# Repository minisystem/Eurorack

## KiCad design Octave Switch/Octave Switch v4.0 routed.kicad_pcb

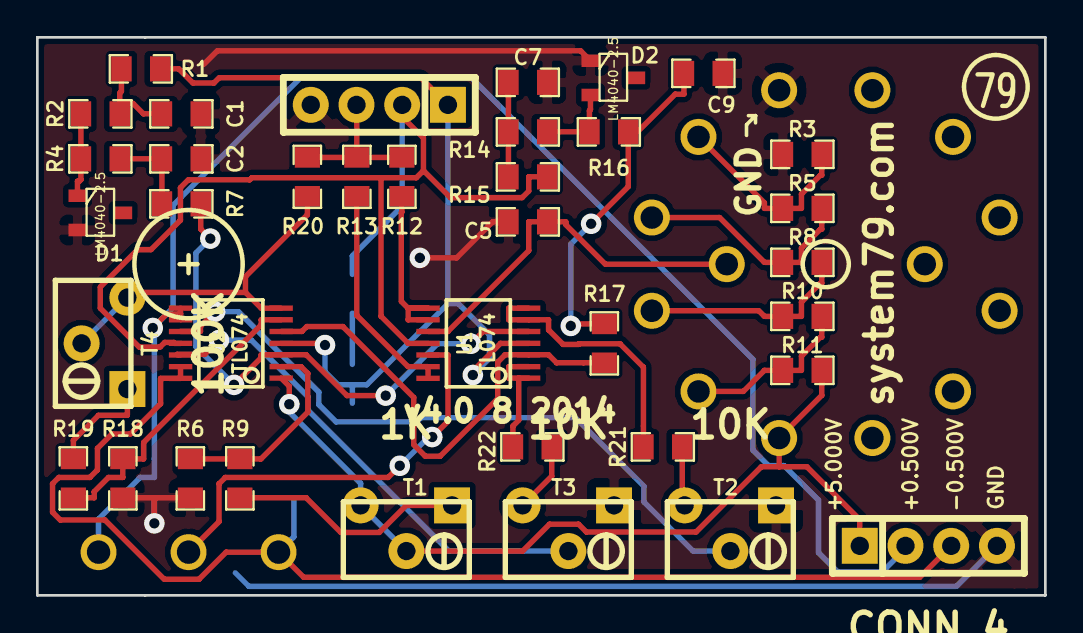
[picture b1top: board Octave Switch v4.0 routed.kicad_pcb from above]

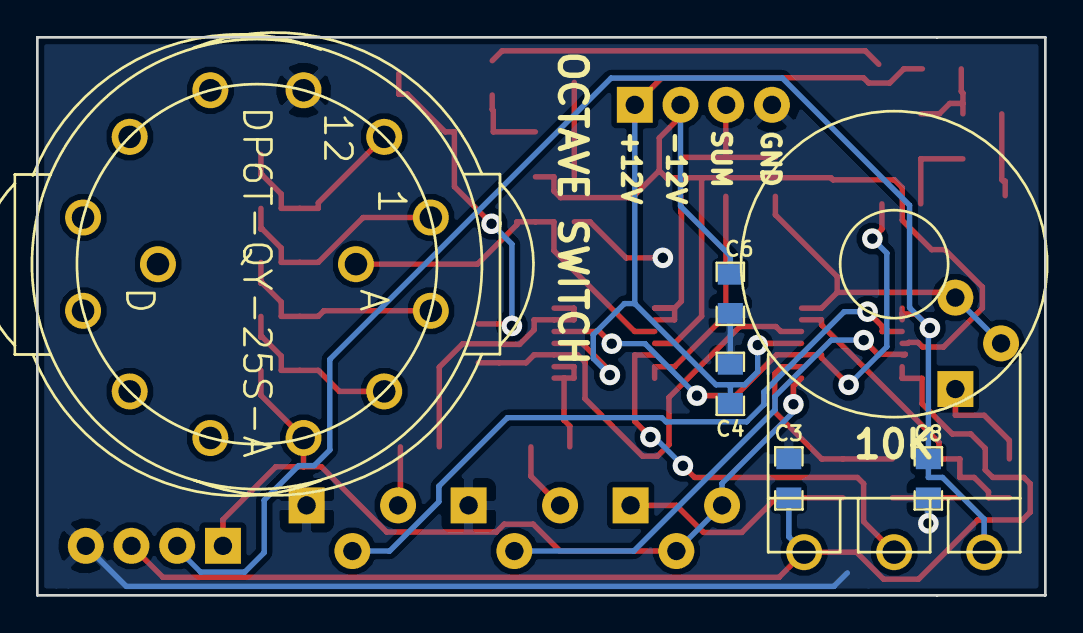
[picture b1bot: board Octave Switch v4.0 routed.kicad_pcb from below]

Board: 2 copper layers, 56.0 x 31.0 mm, 43 parts (6 on the bottom side), 34 nets.

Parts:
C1, C2, C4, C6, C7, C9: 0.1u; SM0805-HAND
C3, C5, C8: 0.001u; SM0805-HAND
D1, D2: LM4040-2.5; SOT23
P1, P2: CONN_4; CONN_0100_X_4
POT1: 10K; RV16A-41
R1, R2, R14, R15: 4.7K; SM0805-HAND
R3, R5, R6, R8, R10, R11: 10K; SM0805-HAND
R4, R7, R16, R17: 33K; SM0805-HAND
R9: 9.53K; SM0805-HAND
R12, R13, R18, R20: 100K; SM0805-HAND
R19: 49.9K; SM0805-HAND
R21, R22: 15K; SM0805-HAND
SW1: DP6T-QY-25S-A; QY-25S-2P6C-JRL
TRIM1: 1K; BI_64W_TRIM
TRIM2, TRIM3: 10K; BI_64W_TRIM
TRIM4: 100K; BI_64W_TRIM
U1, U2: TL074; TSSOP14

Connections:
+0.500V: C8.2, P1.2, POT1.3, U2.8, U2.9
+2.5V: R7.2, U1.5, U2.3
+5.00V: P1.1, R11.2, SW1.4, TRIM1.2, TRIM1.3, U2.1
+12V: C6.1, P2.1, R1.2, U1.4, U2.4
-0.500V: C3.2, P1.3, POT1.1, U2.13, U2.14
-2.5V: R17.2, U1.3, U2.5
-12V: C4.2, P2.2, R15.1, U1.11, U2.11
GND: C1.2, C2.2, C3.1, C4.1, C5.2, C6.2, C7.2, C8.1, C9.2, D1.2, D2.1, P1.4, P2.4, R3.1, R6.1, R18.1, SW1.11, TRIM2.1, TRIM3.1
unnamed: R13.1, U1.13, U1.14
unnamed: C5.1, SW1.A, U1.10
unnamed: D1.1, R2.1, R4.1
unnamed: C1.1, R1.1, R2.2
unnamed: C7.1, R14.1, R15.2
unnamed: D2.2, R14.2, R16.1
unnamed: C9.1, R16.2, R17.1
unnamed: POT1.2, U1.12
unnamed: R5.2, R8.1, SW1.1
unnamed: R8.2, R10.1, SW1.2
unnamed: R10.2, R11.1, SW1.3
unnamed: R12.1, U1.8, U1.9
unnamed: R3.2, R5.1, SW1.12
unnamed: R22.2, TRIM3.3
unnamed: R22.1, U1.1, U1.2
unnamed: R21.2, TRIM2.3
unnamed: R21.1, U1.6, U1.7
unnamed: TRIM3.2, U2.12
unnamed: TRIM2.2, U2.10
unnamed: R20.1, TRIM4.2, TRIM4.3, U2.7
unnamed: R19.2, TRIM4.1
unnamed: R9.2, TRIM1.1
unnamed: R6.2, R9.1, U2.2
unnamed: R18.2, R19.1, U2.6
unnamed: C2.1, R4.2, R7.1
SUM OUT: P2.3, R12.2, R13.2, R20.2

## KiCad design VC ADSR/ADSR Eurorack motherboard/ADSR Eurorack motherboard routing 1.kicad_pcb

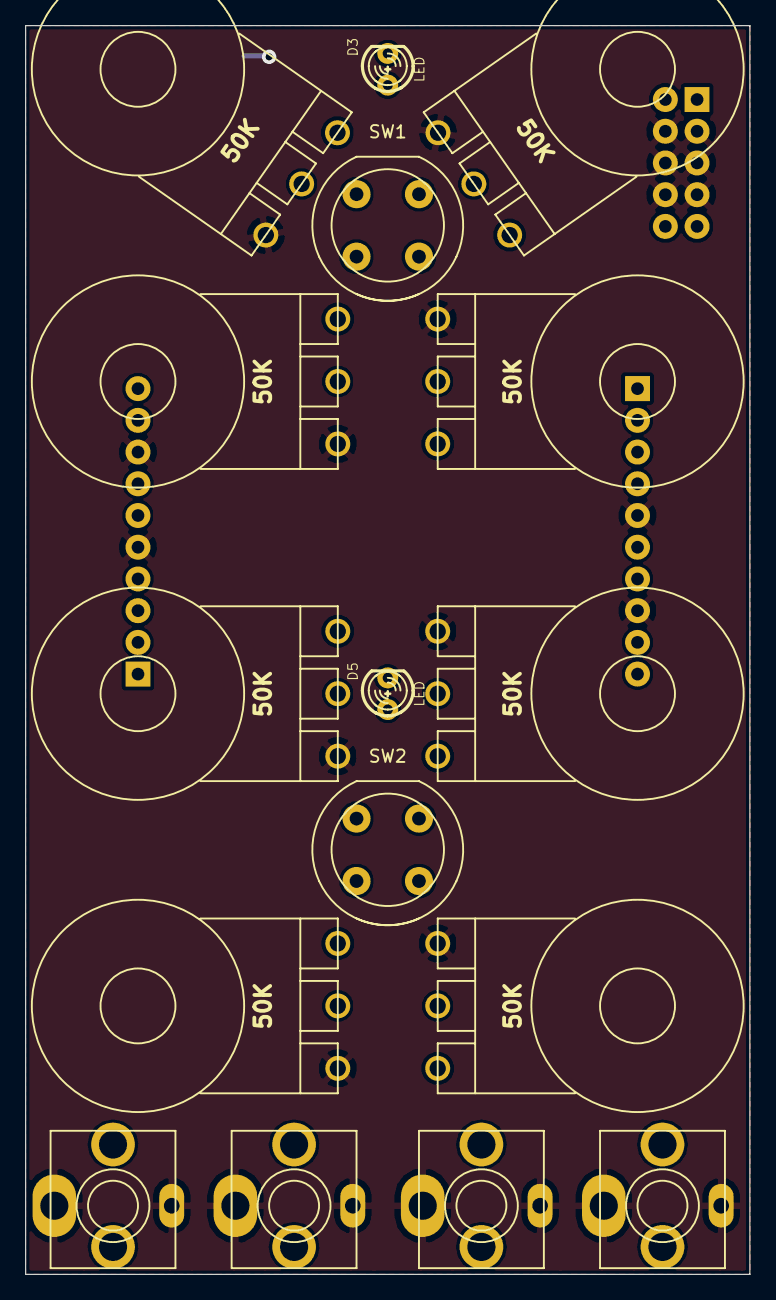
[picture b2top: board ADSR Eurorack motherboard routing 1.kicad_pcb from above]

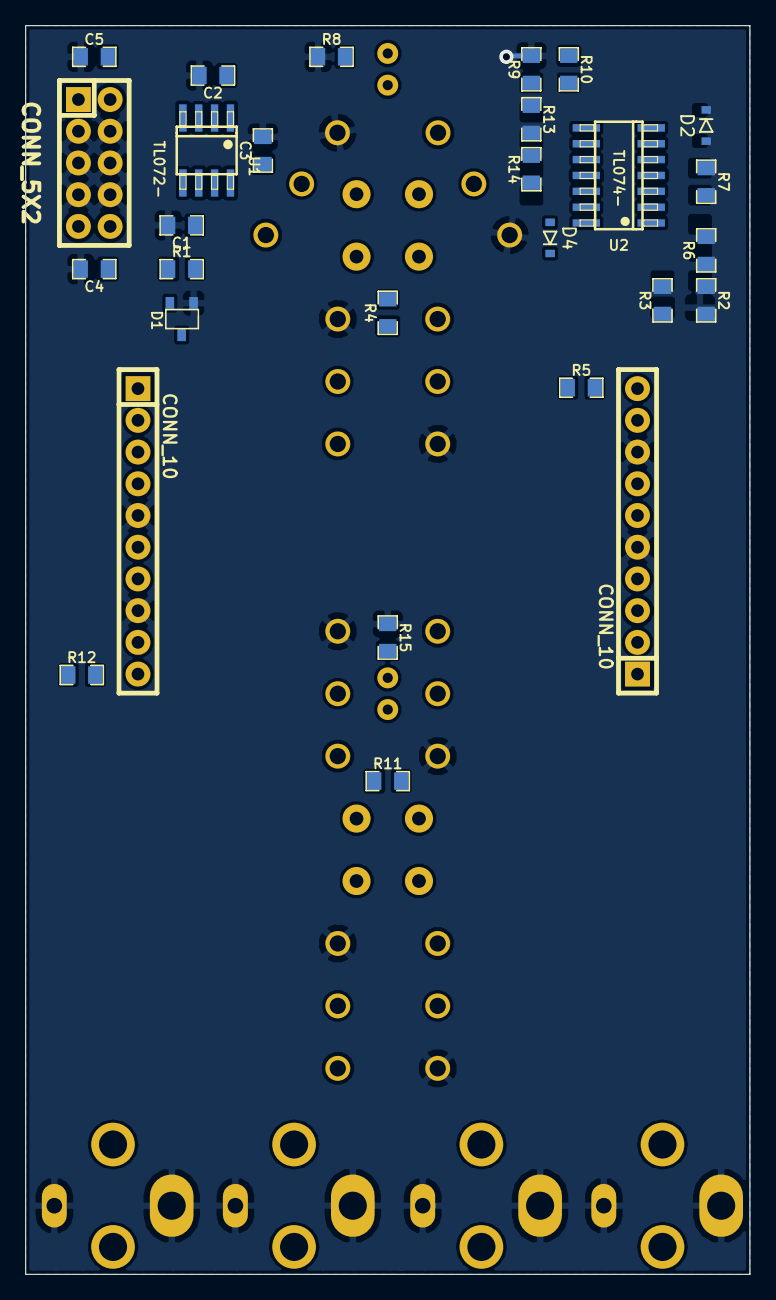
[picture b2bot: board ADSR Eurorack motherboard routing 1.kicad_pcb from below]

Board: 2 copper layers, 58.0 x 100.0 mm, 44 parts (28 on the bottom side), 34 nets.

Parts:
C1, C2, C3: 100n; SM0805-HAND
C4, C5: 1μ; SM0805-HAND
D1: LM4040-5.0; SOT23-JRL
D2, D4: 1N4148; SOD323-JRL
D3, D5: LED; LED-3MM
EG1, EG2: CONN_10; CONN_0100_X_10
J1, J3: OUT1; PJ-301B-JACK
J2, J4: GATE1; PJ-301B-JACK
P1, P2, P3, P4, P5, P6, P7, P8: 50K; RV16A-41
PWR1: CONN_5X2; CONN_0100_2X5_10
R1, R4, R5, R11, R12: 10K; SM0805-HAND
R2, R9: 120K; SM0805-HAND
R3, R10: 330K; SM0805-HAND
R6, R13: 100K; SM0805-HAND
R7, R14: 82K; SM0805-HAND
R8, R15: 270; SM0805-HAND
SW1, SW2: SW_PUSH; KS-01Q-02-JRL
U1: TL072-; SOIC-8-JRL
U2: TL074-; SO14-JRL

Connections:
+5.0V A: C2.1, P1.3, P2.3, P3.3, P4.3, R4.1, U1.1, U1.2
+5.0V B: C3.1, P5.3, P6.3, P7.3, P8.3, R11.1, U1.6, U1.7
+12V: C4.1, EG1.1, EG2.1, PWR1.9, PWR1.10, R1.1, U1.8, U2.4
-12V: C5.2, EG1.3, EG2.3, PWR1.1, PWR1.2, R3.1, R10.1, U1.4, U2.11
ATT1: EG1.9, P1.2
ATT2: EG2.9, P5.2
DEC1: EG1.2, P2.2
DEC2: EG2.2, P6.2
GATE1: EG1.10, R5.2, SW1.2, SW1.4
GATE2: EG2.10, R12.2, SW2.2, SW2.4
GND: C1.2, C2.2, C3.2, C4.2, C5.1, D1.2, EG1.5, EG1.8, EG2.5, EG2.8, J1.1, J2.1, J3.1, J4.1, P1.1, P2.1, P3.1, P4.1, P5.1, P6.1, P7.1, P8.1, PWR1.3, PWR1.4, PWR1.5, PWR1.6, PWR1.7, PWR1.8, R2.2, R8.1, R9.2, R15.1
unnamed: R11.2, SW2.1, SW2.3
unnamed: R2.1, R3.2, R6.1
unnamed: R6.2, R7.1, U2.2
unnamed: D5.2, R15.2
unnamed: R13.2, R14.1, U2.9
unnamed: D4.2, D5.1, U2.14
unnamed: D4.1, U2.13
unnamed: R4.2, SW1.1, SW1.3
unnamed: J4.3, R12.1
unnamed: R9.1, R10.2, R13.1
unnamed: R14.2, U2.8, U2.12
unnamed: J2.3, R5.1
unnamed: D2.1, U2.6
unnamed: R7.2, U2.1, U2.5
unnamed: C1.1, D1.1, R1.2, U1.3, U1.5
unnamed: D3.2, R8.2
unnamed: D2.2, D3.1, U2.7
OUT1: EG1.4, J1.3, U2.3
OUT2: EG2.4, J3.3, U2.10
REL1: EG1.7, P4.2
REL2: EG2.7, P8.2
SUS1: EG1.6, P3.2
SUS2: EG2.6, P7.2

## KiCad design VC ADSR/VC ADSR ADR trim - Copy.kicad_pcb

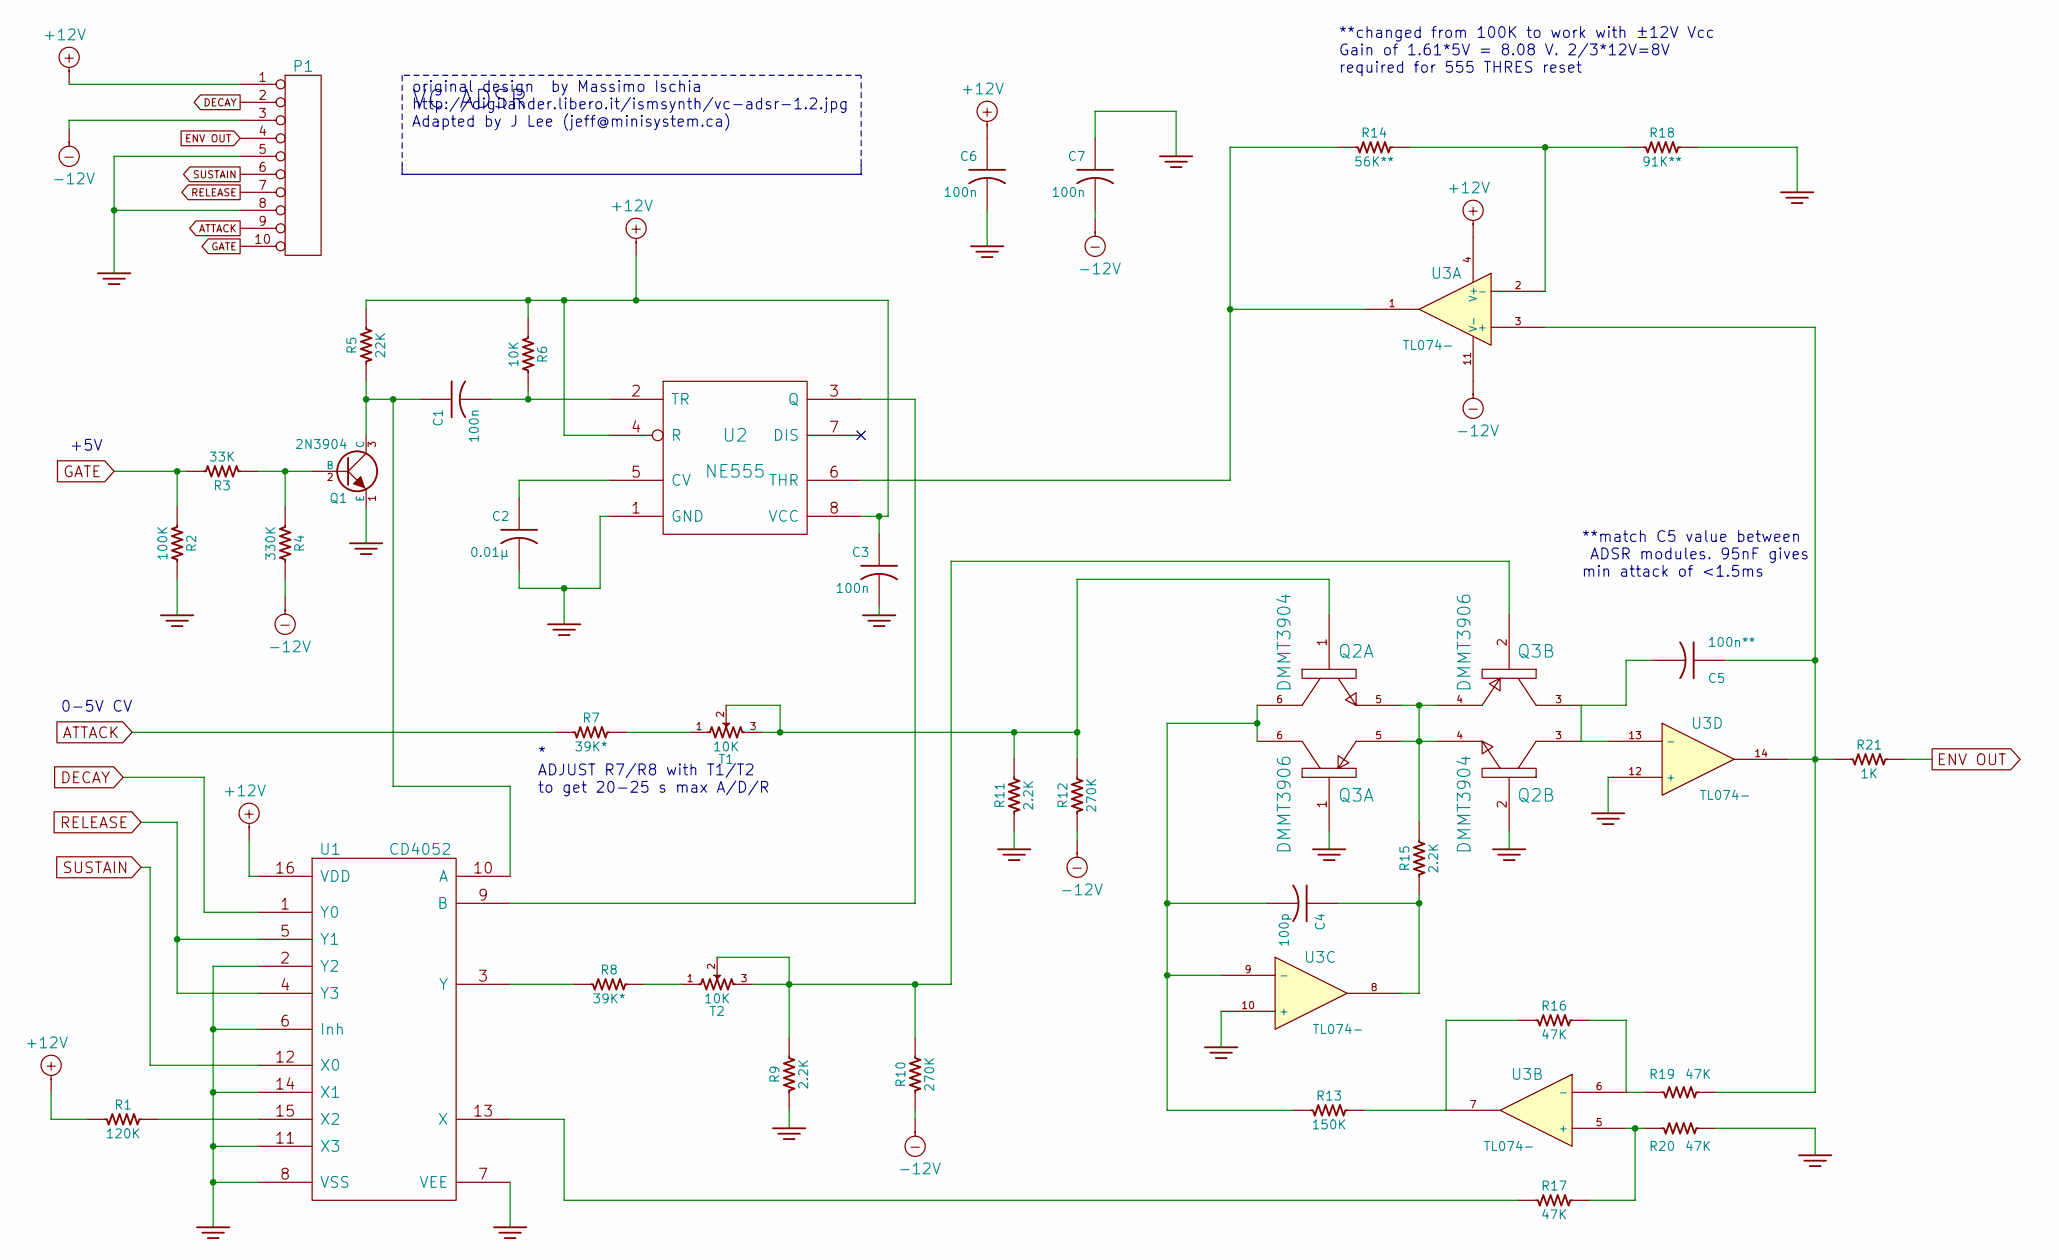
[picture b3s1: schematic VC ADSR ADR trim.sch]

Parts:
C1, C3, C6, C7: 100n
C2: 0.01μ
C4: 100p
C5: 100n**
P1: CONN_10
Q1: 2N3904
Q2: DMMT3904
Q3: DMMT3906
R1: 120K
R2: 100K
R3: 33K
R4: 330K
R5: 22K
R6: 10K
R7, R8: 39K*
R9, R11, R15: 2.2K
R10, R12: 270K
R13: 150K
R14: 56K**
R16, R17, R19, R20: 47K
R18: 91K**
R21: 1K
T1, T2: 10K
U1: CD4052
U2: NE555
U3: TL074-

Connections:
+12V: C3.1, C6.1, P1.1, R1.1, R5.2, R6.1, U1.16 (VDD), U2.4 (R), U2.8 (VCC), U3.4 (V+)
-12V: C7.2, P1.3, R4.2, R10.1, R12.1, U3.11 (V-)
ATTACK: P1.9, R7.1
DECAY: P1.2, U1.1 (Y0)
ENV OUT: P1.4, R21.2
GATE: P1.10, R2.1, R3.2
GND: C2.2, C3.2, C6.2, C7.1, P1.5, P1.8, Q1.1 (E), Q2.2, Q3.1, R2.2, R9.1, R11.1, R18.2, R20.2, U1.2 (Y2), U1.6 (Inh), U1.7 (VEE), U1.8 (VSS), U1.11 (X3), U1.14 (X1), U2.1 (GND), U3.10 (+), U3.12 (+)
unnamed: C1.1, Q1.3 (C), R5.1, U1.10 (A)
unnamed: C1.2, R6.2, U2.2 (TR)
unnamed: C2.1, U2.5 (CV)
unnamed: C4.1, R15.1, U3.8
unnamed: C4.2, Q2.6, Q3.6, R13.1, U3.9 (-)
unnamed: C5.1, R19.2, R21.1, U3.3 (+), U3.14
unnamed: C5.2, Q2.3, Q3.3, U3.13 (-)
unnamed: Q1.2 (B), R3.1, R4.1
unnamed: Q2.4, Q2.5, Q3.4, Q3.5, R15.2
unnamed: R1.2, U1.15 (X2)
unnamed: R8.1, U1.3 (Y)
unnamed: R13.2, R16.1, U3.7
unnamed: R14.1, U2.6 (THR), U3.1
unnamed: R14.2, R18.1, U3.2 (-)
unnamed: R16.2, R19.1, U3.6 (-)
unnamed: R17.1, U1.13 (X)
unnamed: R17.2, R20.1, U3.5 (+)
unnamed: U1.9 (B), U2.3 (Q)
RELEASE: P1.7, U1.4 (Y3), U1.5 (Y1)
SUSTAIN: P1.6, U1.12 (X0)

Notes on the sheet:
**changed from 100K to work with ±12V Vcc Gain of 1.61*5V = 8.08 V. 2/3*12V=8V required for 555 THRES reset
* ADJUST R7/R8 with T1/T2 to get 20-25 s max A/D/R
**match C5 value between ADSR modules. 95nF gives min attack of <1.5ms
0-5V CV
+5V
VC ADSR
original design by Massimo Ischia http://digilander.libero.it/ismsynth/vc-adsr-1.2.jpg Adapted by J Lee (jeff@minisystem.ca)

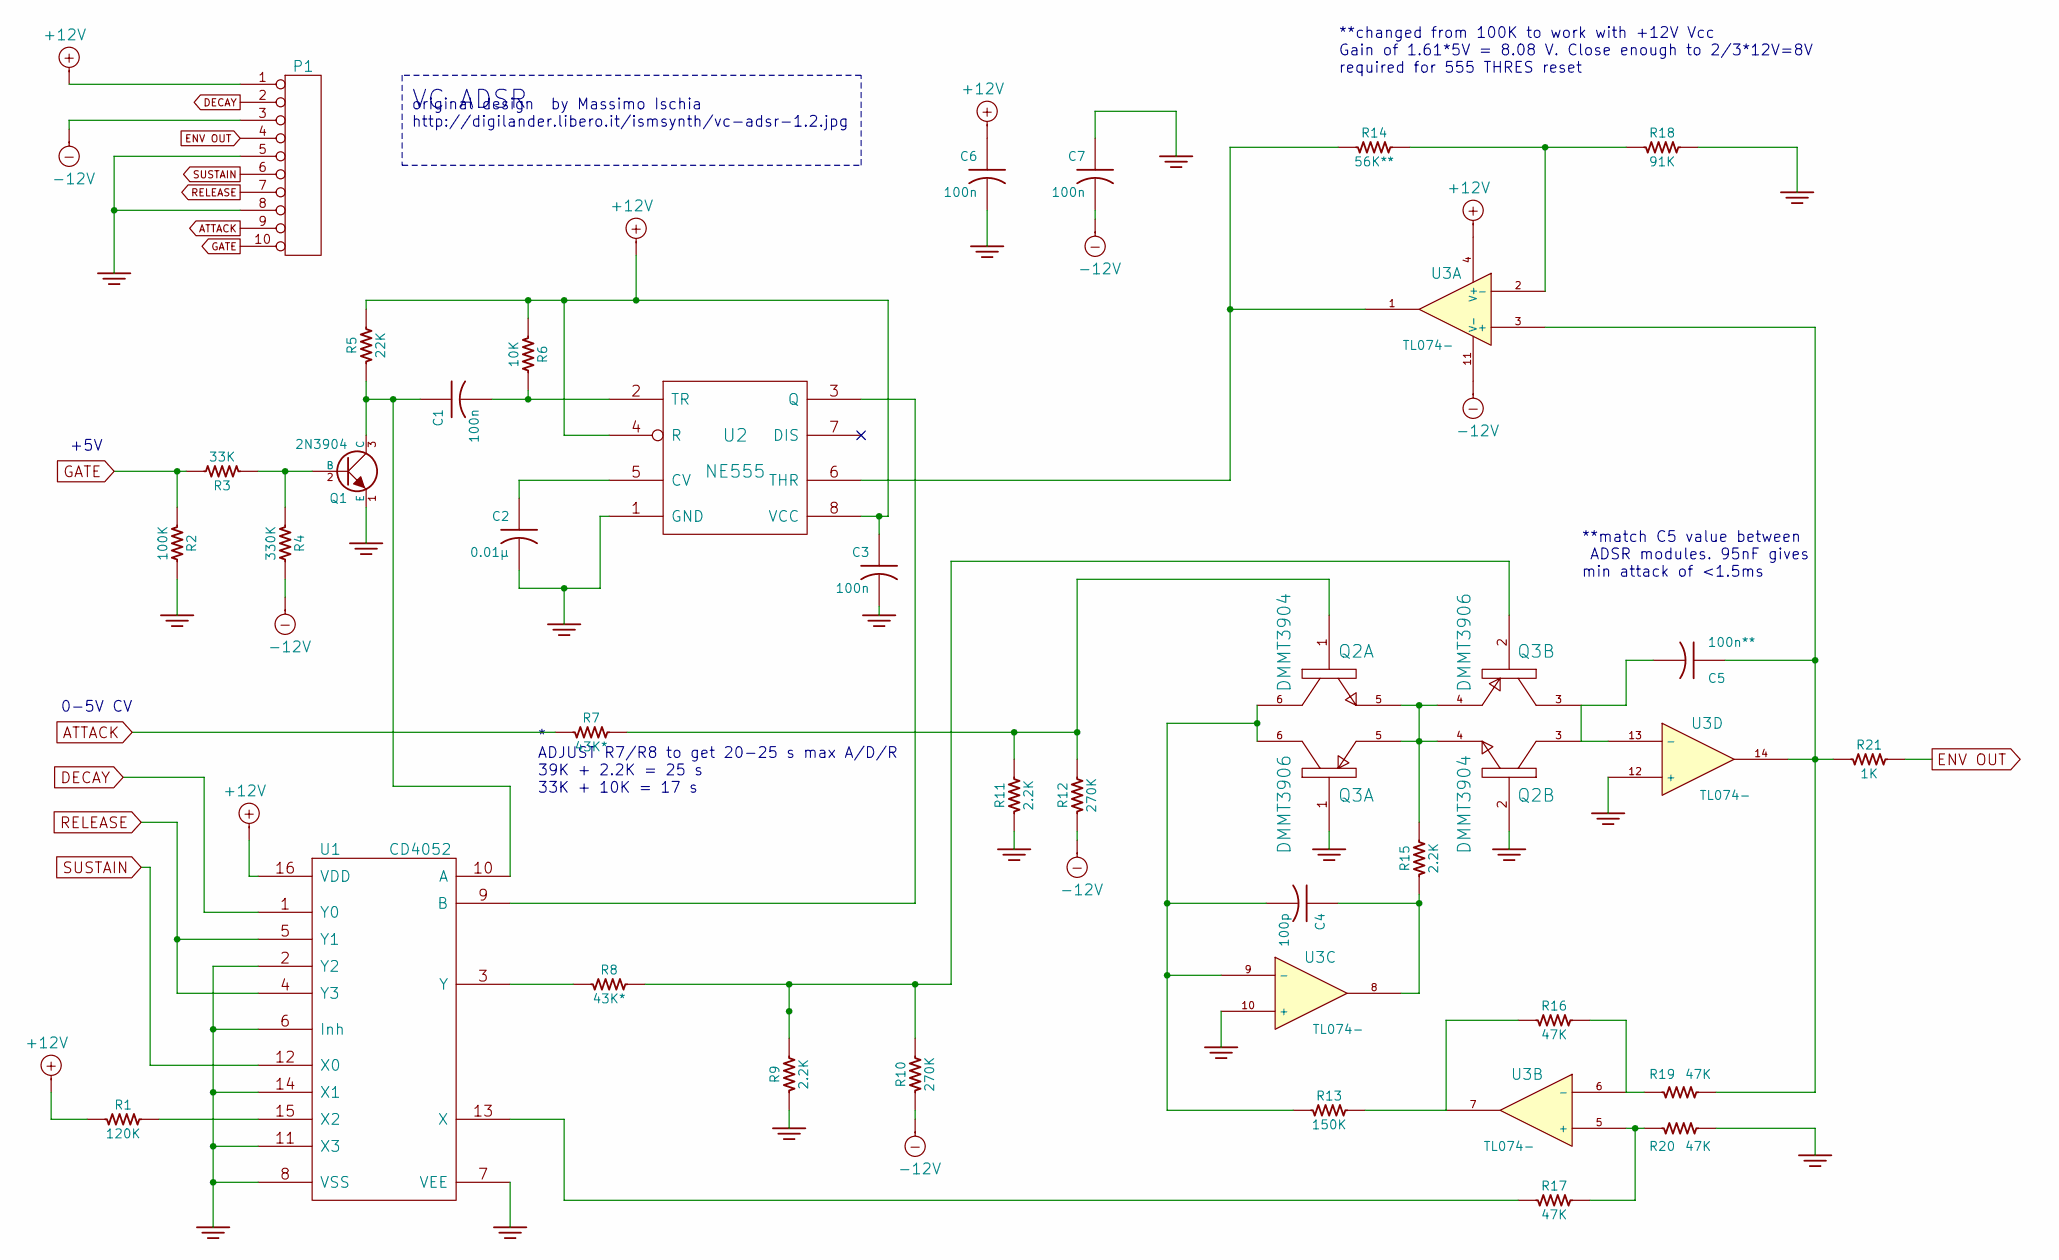
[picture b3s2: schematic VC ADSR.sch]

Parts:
C1, C3, C6, C7: 100n
C2: 0.01μ
C4: 100p
C5: 100n**
P1: CONN_10
Q1: 2N3904
Q2: DMMT3904
Q3: DMMT3906
R1: 120K
R2: 100K
R3: 33K
R4: 330K
R5: 22K
R6: 10K
R7, R8: 43K*
R9, R11, R15: 2.2K
R10, R12: 270K
R13: 150K
R14: 56K**
R16, R17, R19, R20: 47K
R18: 91K
R21: 1K
U1: CD4052
U2: NE555
U3: TL074-

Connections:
+12V: C3.1, C6.1, P1.1, R1.1, R5.2, R6.1, U1.16 (VDD), U2.4 (R), U2.8 (VCC), U3.4 (V+)
-12V: C7.2, P1.3, R4.2, R10.1, R12.1, U3.11 (V-)
ATTACK: P1.9, R7.1
DECAY: P1.2, U1.1 (Y0)
ENV OUT: P1.4, R21.2
GATE: P1.10, R2.1, R3.2
GND: C2.2, C3.2, C6.2, C7.1, P1.5, P1.8, Q1.1 (E), Q2.2, Q3.1, R2.2, R9.1, R11.1, R18.2, R20.2, U1.2 (Y2), U1.6 (Inh), U1.7 (VEE), U1.8 (VSS), U1.11 (X3), U1.14 (X1), U2.1 (GND), U3.10 (+), U3.12 (+)
unnamed: C1.1, Q1.3 (C), R5.1, U1.10 (A)
unnamed: C1.2, R6.2, U2.2 (TR)
unnamed: C2.1, U2.5 (CV)
unnamed: C4.1, R15.1, U3.8
unnamed: C4.2, Q2.6, Q3.6, R13.1, U3.9 (-)
unnamed: C5.1, R19.2, R21.1, U3.3 (+), U3.14
unnamed: C5.2, Q2.3, Q3.3, U3.13 (-)
unnamed: Q1.2 (B), R3.1, R4.1
unnamed: Q2.4, Q2.5, Q3.4, Q3.5, R15.2
unnamed: R1.2, U1.15 (X2)
unnamed: R8.1, U1.3 (Y)
unnamed: R13.2, R16.1, U3.7
unnamed: R14.1, U2.6 (THR), U3.1
unnamed: R14.2, R18.1, U3.2 (-)
unnamed: R16.2, R19.1, U3.6 (-)
unnamed: R17.1, U1.13 (X)
unnamed: R17.2, R20.1, U3.5 (+)
unnamed: U1.9 (B), U2.3 (Q)
RELEASE: P1.7, U1.4 (Y3), U1.5 (Y1)
SUSTAIN: P1.6, U1.12 (X0)

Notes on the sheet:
**changed from 100K to work with +12V Vcc Gain of 1.61*5V = 8.08 V. Close enough to 2/3*12V=8V required for 555 THRES reset
* ADJUST R7/R8 to get 20-25 s max A/D/R 39K + 2.2K = 25 s 33K + 10K = 17 s
**match C5 value between ADSR modules. 95nF gives min attack of <1.5ms
0-5V CV
+5V
VC ADSR
original design by Massimo Ischia http://digilander.libero.it/ismsynth/vc-adsr-1.2.jpg

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
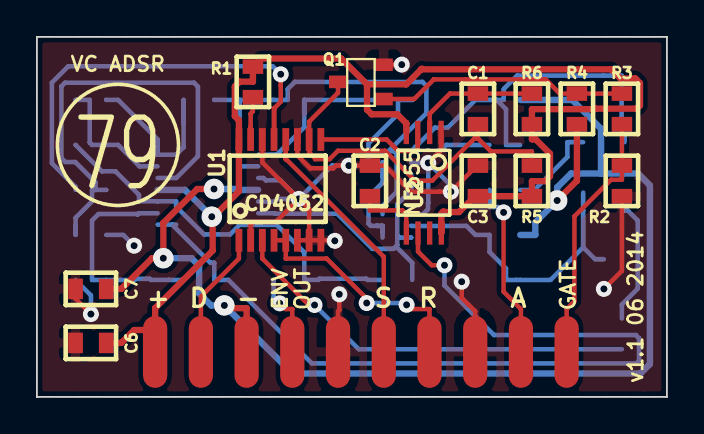
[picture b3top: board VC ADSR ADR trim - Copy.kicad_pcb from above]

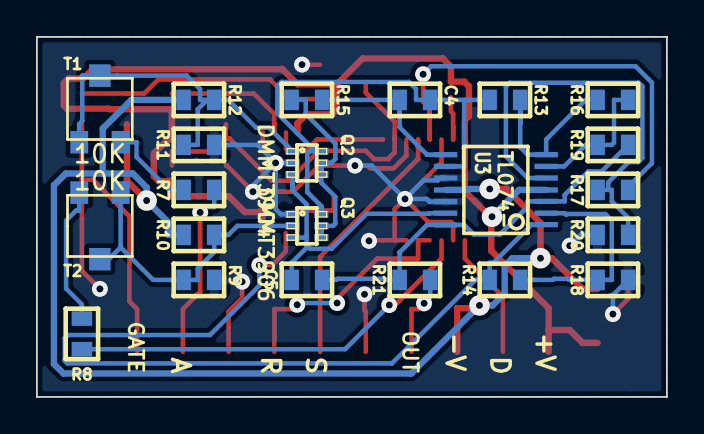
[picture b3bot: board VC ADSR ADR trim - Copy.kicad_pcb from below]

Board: 2 copper layers, 35.0 x 20.0 mm, 37 parts (22 on the bottom side), 31 nets.
